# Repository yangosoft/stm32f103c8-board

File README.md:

# stm32f103c8-board

Quick demo board made with Eagle and working with GCC G++ OpenCM3 Makefile FreeRTOS CAN

This project runs FreeRTOS 8.2.1 with OpenCM3  through STM32F103C8, a cheap ARM 32bits Cortex M3, in a custom board designed with Eagle 7.

v5 files:
This revision removes ground plane and improves routing. There is a CH340G for USB<->Serial communication.
I need to improve USB and CAN since they share lines

## STM32F103RB6

It also contains a port of FreeRTOS 8.2.1 with OpenCM3 and C++ support for cheap eBay boards with STM32F103RB6 and LCD screens like http://hackaday.com/2012/11/07/developing-with-ebay-sourced-arm-lcd-dev-boards/

Mine came named as MINI-STM32-V3 and a label with www.openmcu.com, a 2.8" TFT LCD Rev2.

Zizzle http://zizzle-brewbot.blogspot.com.es/2012/10/stm32-lcd-touch-screen-demo.html has done a better work with FreeRTOS 7 and Eclipse.

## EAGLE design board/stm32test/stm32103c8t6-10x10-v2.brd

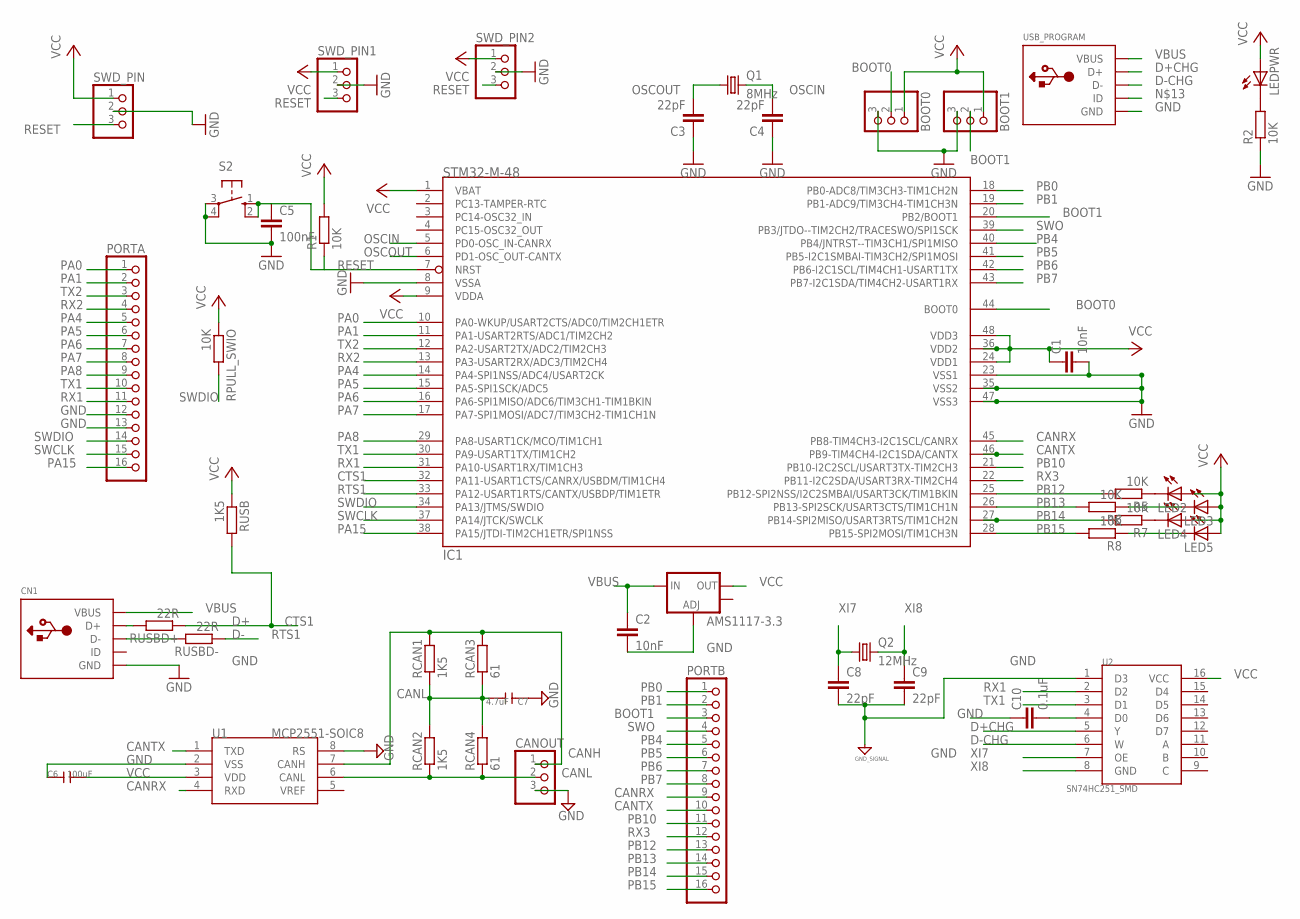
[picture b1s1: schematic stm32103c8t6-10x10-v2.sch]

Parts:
AMS1117-3.3: V_REG_LM1117SOT223; SOT223
BOOT0, BOOT1: PINHD-1X3; 1X03
C1: 10nF; C1210
C2: 10nF; C1206
C3, C4: 22pF; C1210
C5: 100nF; C1206
C6: 100uF; C1206
C7: 4.7uF; C1206
C8, C9: 22pF; C1206
C10: 0.1uF; C1206
CANOUT: PINHD-1X3; 1X03
CN1: USBTHM; USB-MINIB-THM
IC1: STM32-M-48; LQFP48
LED2, LED3, LED4, LED5: LEDSMT1206; 1206
LEDPWR: LEDSMT1206; 1206
PORTA: PINHD-1X16; 1X16
PORTB: PINHD-1X16; 1X16
Q1: 8MHz; HC49/S
Q2: 12MHz; HC49/S
R1, R2, R5, R6, R7, R8: 10K; R1206
RCAN1, RCAN2: 1K5; R1206
RCAN3, RCAN4: 61; R1206
RPULL_SWIO: 10K; R1206
RUSB: 1K5; R1206
RUSBD+: 22R; R1206
RUSBD-: 22R; R1206
S2: 10-XX; B3F-10XX
SWD_PIN, SWD_PIN1, SWD_PIN2: PINHD-1X3; 1X03
U1: MCP2551-SOIC8; SOIC8-6.0
U2: SN74HC251_SMD; SO016
USB_PROGRAM: USBTHM; USB-MINIB-THM

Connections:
BOOT0: BOOT0.2, IC1.44 (BOOT0)
BOOT1: BOOT1.2, IC1.20 (PB2/BOOT1), PORTB.3
CANH: CANOUT.1, RCAN1.2, RCAN3.2, U1.7 (CANH)
CANL: CANOUT.2, RCAN2.1, RCAN4.1, U1.6 (CANL)
CANRX: IC1.45 (PB8-TIM4CH3-I2C1SCL/CANRX), PORTB.9, U1.4 (RXD)
CANTX: IC1.46 (PB9-TIM4CH4-I2C1SDA/CANTX), PORTB.10, U1.1 (TXD)
CTS1: IC1.32 (PA11-USART1CTS/CANRX/USBDM/TIM1CH4), RUSB.2, RUSBD+.1
D+: CN1.D+, RUSBD+.2
D+CHG: U2.5 (Y), USB_PROGRAM.D+
D-: CN1.D-, RUSBD-.2
D-CHG: U2.6 (W), USB_PROGRAM.D-
GND: AMS1117-3.3.1 (ADJ), BOOT0.3, BOOT1.3, C1.2, C2.2, C3.1, C4.1, C5.2, C6.1, C7.1, C8.2, C9.2, C10.1, CANOUT.3, CN1.GND, IC1.8 (VSSA), IC1.23 (VSS1), IC1.35 (VSS2), IC1.47 (VSS3), PORTA.12, PORTA.13, R2.1, S2.3, S2.4 (P1), SWD_PIN.2, SWD_PIN1.2, SWD_PIN2.2, U1.2 (VSS), U1.8 (RS), U2.1 (D3), USB_PROGRAM.GND
unnamed: LEDPWR.C, R2.2
unnamed: LED2.C, R5.1
unnamed: LED3.C, R6.1
unnamed: LED4.C, R7.1
unnamed: LED5.C, R8.1
unnamed: C10.2, U2.4 (D0)
OSCIN: C4.2, IC1.5 (PD0-OSC_IN-CANRX), Q1.2
OSCOUT: C3.2, IC1.6 (PD1-OSC_OUT-CANTX), Q1.1
PA0: IC1.10 (PA0-WKUP/USART2CTS/ADC0/TIM2CH1ETR), PORTA.1
PA1: IC1.11 (PA1-USART2RTS/ADC1/TIM2CH2), PORTA.2
PA4: IC1.14 (PA4-SPI1NSS/ADC4/USART2CK), PORTA.5
PA5: IC1.15 (PA5-SPI1SCK/ADC5), PORTA.6
PA6: IC1.16 (PA6-SPI1MISO/ADC6/TIM3CH1-TIM1BKIN), PORTA.7
PA7: IC1.17 (PA7-SPI1MOSI/ADC7/TIM3CH2-TIM1CH1N), PORTA.8
PA8: IC1.29 (PA8-USART1CK/MCO/TIM1CH1), PORTA.9
PA15: IC1.38 (PA15/JTDI-TIM2CH1ETR/SPI1NSS), PORTA.16
PB0: IC1.18 (PB0-ADC8/TIM3CH3-TIM1CH2N), PORTB.1
PB1: IC1.19 (PB1-ADC9/TIM3CH4-TIM1CH3N), PORTB.2
PB4: IC1.40 (PB4/JNTRST--TIM3CH1/SPI1MISO), PORTB.5
PB5: IC1.41 (PB5-I2C1SMBAI-TIM3CH2/SPI1MOSI), PORTB.6
PB6: IC1.42 (PB6-I2C1SCL/TIM4CH1-USART1TX), PORTB.7
PB7: IC1.43 (PB7-I2C1SDA/TIM4CH2-USART1RX), PORTB.8
PB10: IC1.21 (PB10-I2C2SCL/USART3TX-TIM2CH3), PORTB.11
PB12: IC1.25 (PB12-SPI2NSS/I2C2SMBAI/USART3CK/TIM1BKIN), PORTB.13, R5.2
PB13: IC1.26 (PB13-SPI2SCK/USART3CTS/TIM1CH1N), PORTB.14, R6.2
PB14: IC1.27 (PB14-SPI2MISO/USART3RTS/TIM1CH2N), PORTB.15, R7.2
PB15: IC1.28 (PB15-SPI2MOSI/TIM1CH3N), PORTB.16, R8.2
RESET: C5.1, IC1.7 (NRST), R1.1, S2.1 (S), S2.2 (S1), SWD_PIN.3, SWD_PIN1.3, SWD_PIN2.3
RTS1: IC1.33 (PA12-USART1RTS/CANTX/USBDP/TIM1ETR), RUSBD-.1
RX1: IC1.31 (PA10-USART1RX/TIM1CH3), PORTA.11, U2.2 (D2)
RX2: IC1.13 (PA3-USART2RX/ADC3/TIM2CH4), PORTA.4
RX3: IC1.22 (PB11-I2C2SDA/USART3RX-TIM2CH4), PORTB.12
SWCLK: IC1.37 (PA14/JTCK/SWCLK), PORTA.15
SWDIO: IC1.34 (PA13/JTMS/SWDIO), PORTA.14, RPULL_SWIO.2
SWO: IC1.39 (PB3/JTDO--TIM2CH2/TRACESWO/SPI1SCK), PORTB.4
TX1: IC1.30 (PA9-USART1TX/TIM1CH2), PORTA.10, U2.3 (D1)
TX2: IC1.12 (PA2-USART2TX/ADC2/TIM2CH3), PORTA.3
UNIC: C7.2, RCAN1.1, RCAN2.2, RCAN3.1, RCAN4.2
VBUS: AMS1117-3.3.3 (IN), C2.1, CN1.VBUS, USB_PROGRAM.VBUS
VCC: AMS1117-3.3.2 (OUT), BOOT0.1, BOOT1.1, C1.1, C6.2, IC1.1 (VBAT), IC1.9 (VDDA), IC1.24 (VDD1), IC1.36 (VDD2), IC1.48 (VDD3), LED2.A, LED3.A, LED4.A, LED5.A, LEDPWR.A, R1.2, RPULL_SWIO.1, RUSB.1, SWD_PIN.1, SWD_PIN1.1, SWD_PIN2.1, U1.3 (VDD), U2.16 (VCC)
XI7: C8.1, Q2.1, U2.7 (OE)
XI8: C9.1, Q2.2, U2.8 (GND)

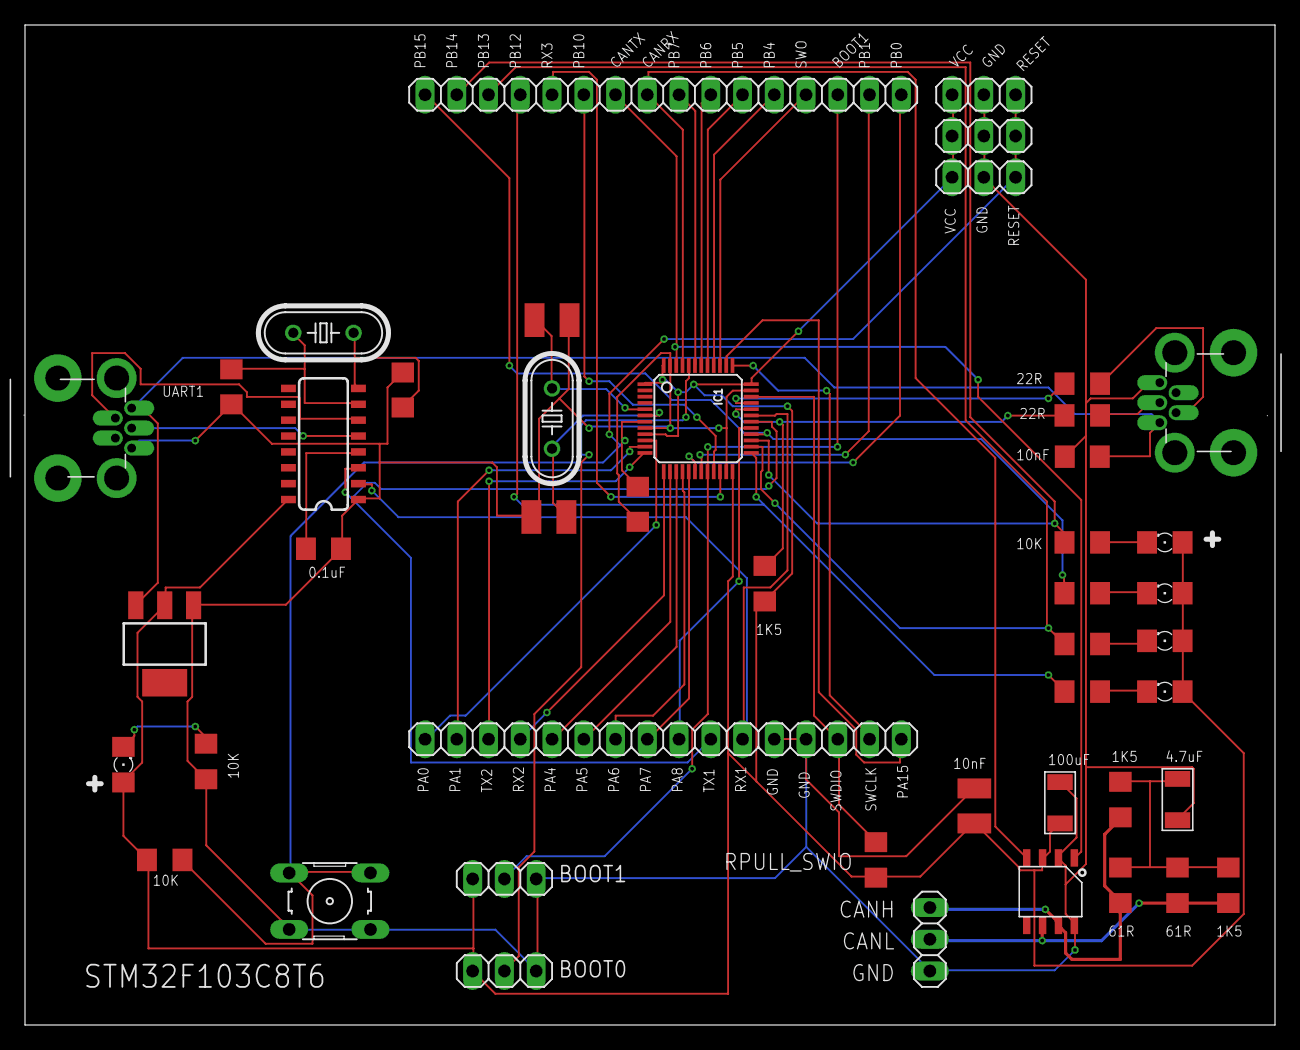
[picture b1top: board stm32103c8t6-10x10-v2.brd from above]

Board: 2 copper layers, 100.0 x 80.0 mm, 46 parts (0 on the bottom side), 54 nets.

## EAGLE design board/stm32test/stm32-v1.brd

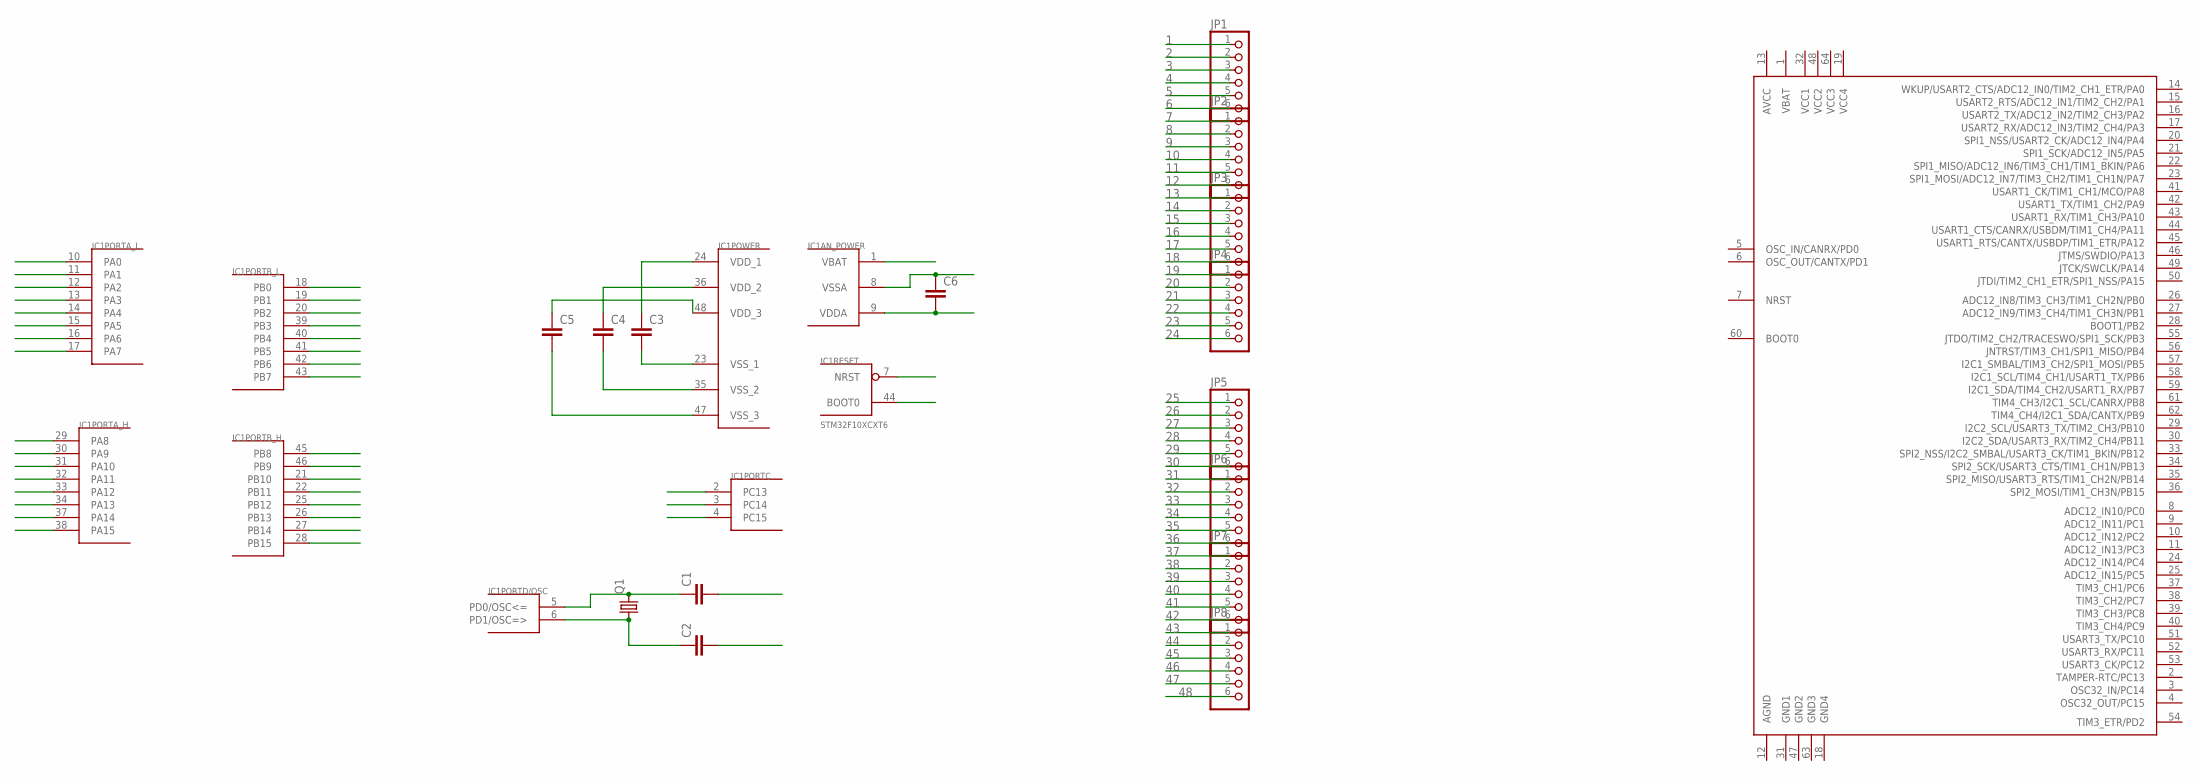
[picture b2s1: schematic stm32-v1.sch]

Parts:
C1, C2, C3, C4, C5, C6: CAP1206; 1206
IC1: STM32F10XCXT6; TQFP48
JP1, JP2, JP3, JP4, JP5, JP6, JP7, JP8: PINHD-1X6; 1X06
Q1: CRYSTAL5X3; CRYSTAL-SMD-5X3
U$2: STM32F103X8/B; LQFP64

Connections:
1: IC1.1 (VBAT), JP1.1
2: IC1.2 (PC13), JP1.2
3: IC1.3 (PC14), JP1.3
4: IC1.4 (PC15), JP1.4
5: C1.2, JP1.5
6: C2.2, JP1.6
7: IC1.7 (NRST), JP2.1
8: C6.1, IC1.8 (VSSA), JP2.2
9: C6.2, IC1.9 (VDDA), JP2.3
10: IC1.10 (PA0), JP2.4
11: IC1.11 (PA1), JP2.5
12: IC1.12 (PA2), JP2.6
13: IC1.13 (PA3), JP3.1
14: IC1.14 (PA4), JP3.2
15: IC1.15 (PA5), JP3.3
16: IC1.16 (PA6), JP3.4
17: IC1.17 (PA7), JP3.5
18: IC1.18 (PB0), JP3.6
19: IC1.19 (PB1), JP4.1
20: IC1.20 (PB2), JP4.2
21: IC1.21 (PB10), JP4.3
22: IC1.22 (PB11), JP4.4
23: C3.2, IC1.23 (VSS_1), JP4.5
24: C3.1, IC1.24 (VDD_1), JP4.6
25: IC1.25 (PB12), JP5.1
26: IC1.26 (PB13), JP5.2
27: IC1.27 (PB14), JP5.3
28: IC1.28 (PB15), JP5.4
29: IC1.29 (PA8), JP5.5
30: IC1.30 (PA9), JP5.6
31: IC1.31 (PA10), JP6.1
32: IC1.32 (PA11), JP6.2
33: IC1.33 (PA12), JP6.3
34: IC1.34 (PA13), JP6.4
35: C4.2, IC1.35 (VSS_2), JP6.5
36: C4.1, IC1.36 (VDD_2), JP6.6
37: IC1.37 (PA14), JP7.1
38: IC1.38 (PA15), JP7.2
39: IC1.39 (PB3), JP7.3
40: IC1.40 (PB4), JP7.4
41: IC1.41 (PB5), JP7.5
42: IC1.42 (PB6), JP7.6
43: IC1.43 (PB7), JP8.1
44: IC1.44 (BOOT0), JP8.2
45: IC1.45 (PB8), JP8.3
46: IC1.46 (PB9), JP8.4
47: C5.2, IC1.47 (VSS_3), JP8.5
48: C5.1, IC1.48 (VDD_3), JP8.6
unnamed: C1.1, IC1.5 (PD0/OSC<=), Q1.3 (2)
unnamed: C2.1, IC1.6 (PD1/OSC=>), Q1.1

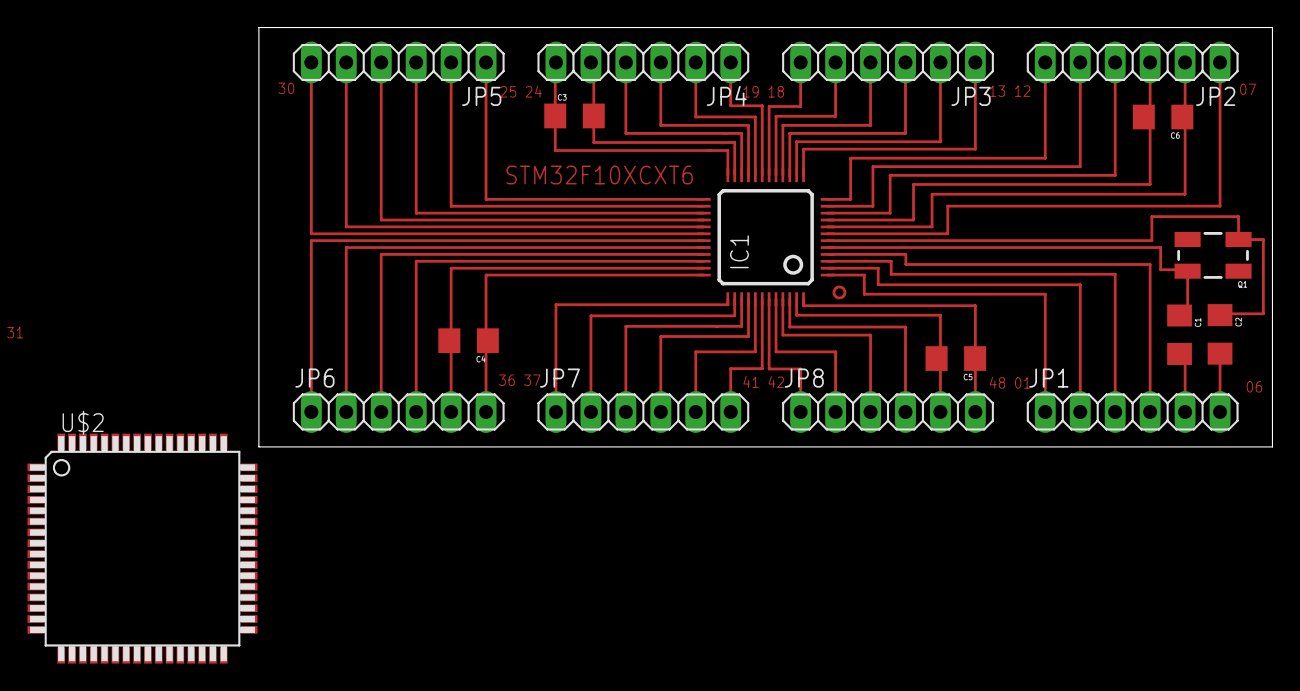
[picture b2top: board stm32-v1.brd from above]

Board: 2 copper layers, 73.7 x 30.5 mm, 17 parts (0 on the bottom side), 50 nets.

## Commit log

2015-07-28 Initial code and board
2015-07-29 Added FreeRTOS 8 for cheap eBay boards with stm32f103rb6
2015-07-29 Updated description
2015-07-30 Added revision 4 with CH340G USB Serial
2015-09-07 Removed ground plane
2015-09-07 v5. Removed ground plane and improved layout
2015-09-10 Revision 7 with fixed CH340G. Removed UART connectors and changed CAN pins
2015-09-16 Added new layout 10cm x 8cm
2015-11-19 Upgrade design to 10x10 v2
2015-11-20 Changed link script. STM32F103C8 has 20K of flash

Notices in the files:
parts and their libraries:
SparkFun-PowerIC: Licensing: Creative Commons ShareAlike 4.0 International - https://creativecommons.org/licenses/by-sa/4.0
SparkFun-DigitalIC: Licensing: CC v3.0 Share-Alike You are welcome to use this library for commercial purposes.
